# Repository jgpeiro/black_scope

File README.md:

# Black_scope
Low end oscilloscope based on STM32G4

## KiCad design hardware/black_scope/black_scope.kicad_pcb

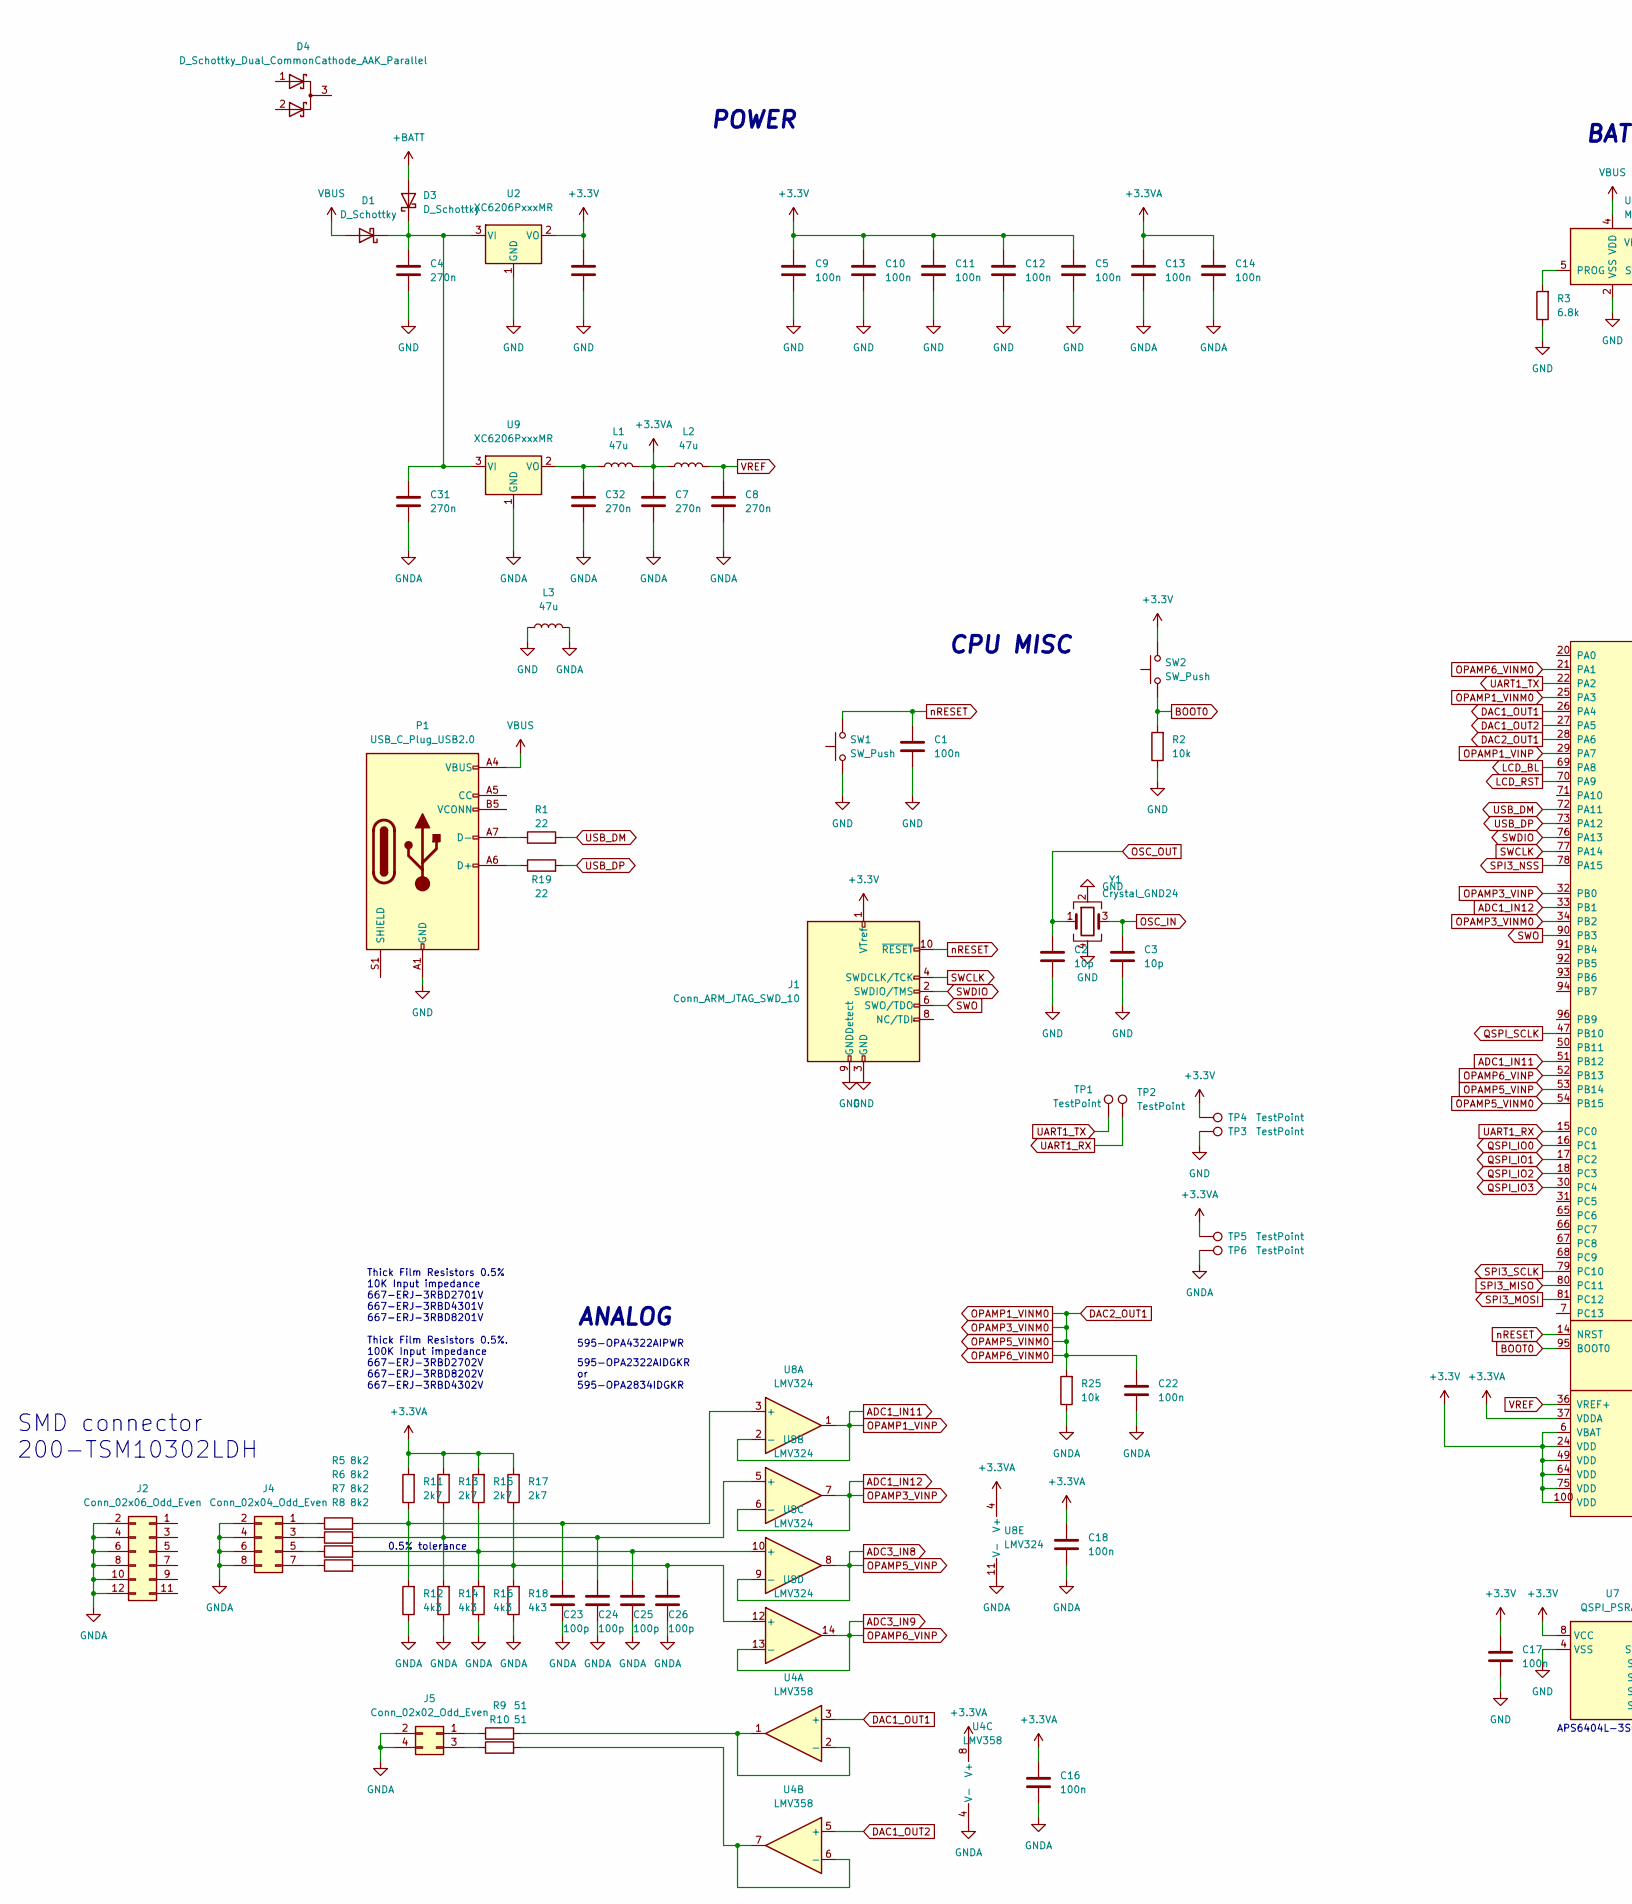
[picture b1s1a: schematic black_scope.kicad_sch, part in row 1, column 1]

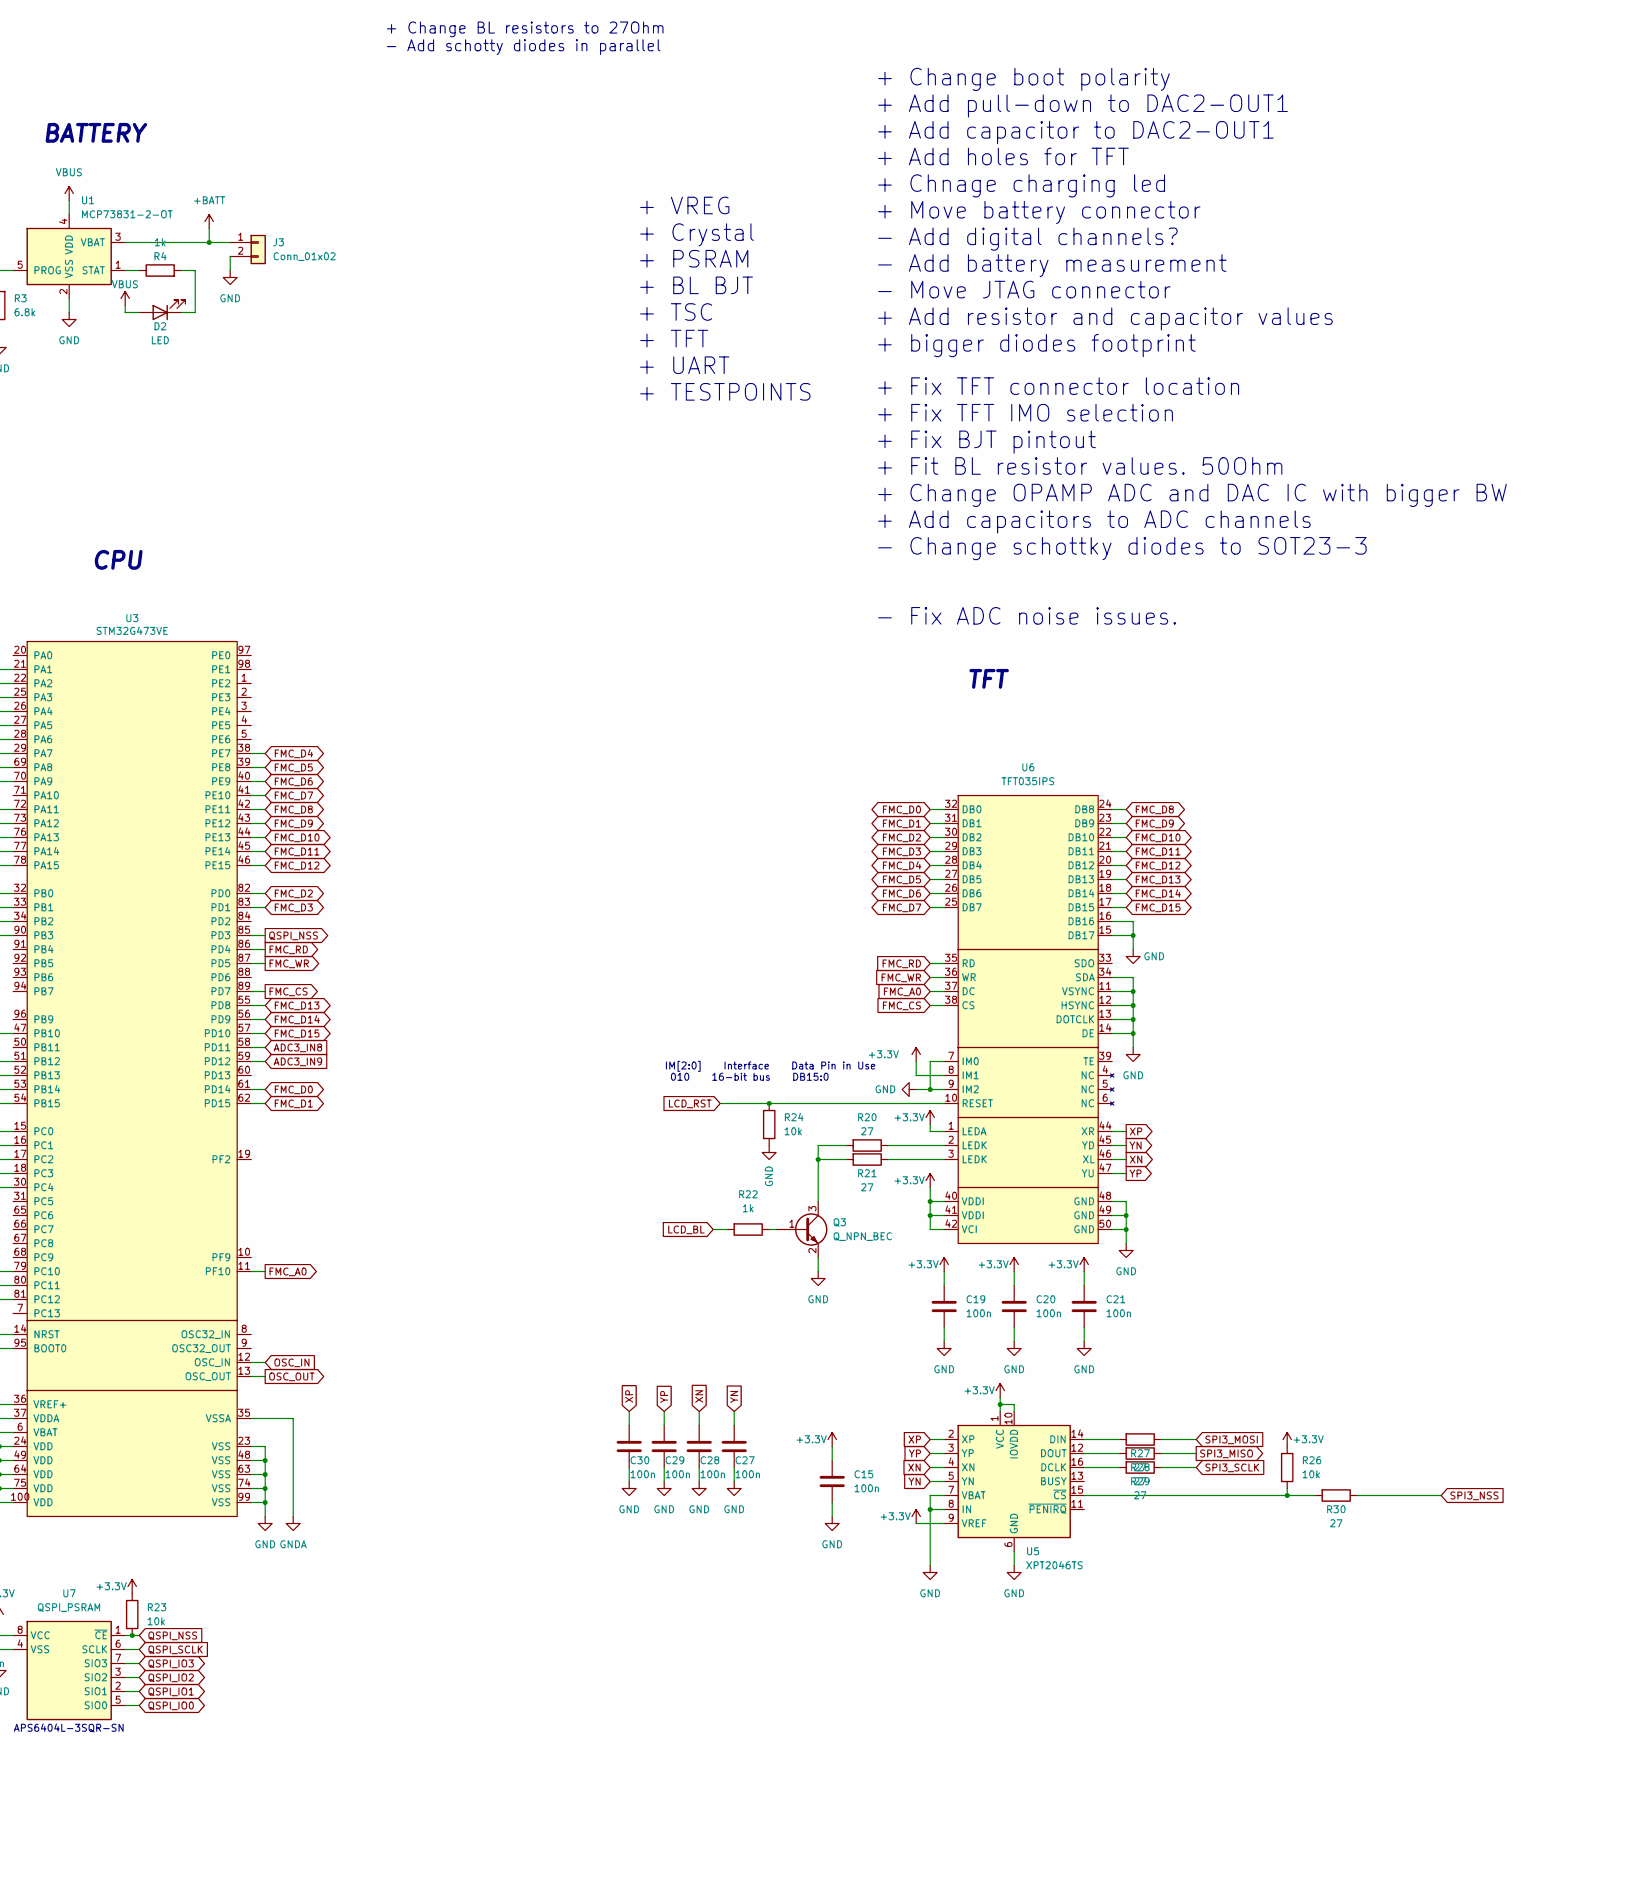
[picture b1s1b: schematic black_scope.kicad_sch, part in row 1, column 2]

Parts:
C1, C5, C9, C10, C11, C12, C13, C14, C15, C16, C17, C18, C19, C20, C21, C22, C27, C28, C29, C30: 100n; C_0603_1608Metric_Pad1.08x0.95mm_HandSolder
C2, C3: 10p; C_0603_1608Metric_Pad1.08x0.95mm_HandSolder
C4, C6, C7, C8, C31, C32: 270n; C_0603_1608Metric_Pad1.08x0.95mm_HandSolder
C23, C24, C25, C26: 100p; C_0603_1608Metric_Pad1.08x0.95mm_HandSolder
D1, D3: D_Schottky; D_1206_3216Metric_Pad1.42x1.75mm_HandSolder; Mouser REF 512-SS24FL
D2: LED; D_0603_1608Metric_Pad1.05x0.95mm_HandSolder
D4: D_Schottky_Dual_CommonCathode_AAK_Parallel; SOT-23; Mouser REF 750-BAT54C-HF
J1: Conn_ARM_JTAG_SWD_10; PinHeader_2x05_P1.27mm_Vertical_SMD; Mouser REF 649-221121-00010T4LF
J2: Conn_02x06_Odd_Even; PinHeader_2x06_P2.54mm_Vertical_SMD; Mouser REF 200-TSM10302LDH
J3: Conn_01x02; JST_PH_B2B-PH-K_1x02_P2.00mm_Vertical
J4: Conn_02x04_Odd_Even; PinHeader_2x04_P2.54mm_Horizontal
J5: Conn_02x02_Odd_Even; PinHeader_2x02_P2.54mm_Horizontal
L1, L2, L3: 47u; L_0603_1608Metric_Pad1.05x0.95mm_HandSolder; Mouser REF 80-L0603B470KPWFT
P1: USB_C_Plug_USB2.0; USB_C_Receptacle_HRO_TYPE-C-31-M-12; Mouser REF 640-USB4105-GF-A
Q3: Q_NPN_BEC; SOT-23; Mouser REF 750-SS8050-G
R1, R19: 22; R_0603_1608Metric_Pad0.98x0.95mm_HandSolder
R2, R23, R24, R25, R26: 10k; R_0603_1608Metric_Pad0.98x0.95mm_HandSolder
R3: 6.8k; R_0603_1608Metric_Pad0.98x0.95mm_HandSolder
R4, R22: 1k; R_0603_1608Metric_Pad0.98x0.95mm_HandSolder
R5, R6, R7, R8: 8k2; R_0603_1608Metric_Pad0.98x0.95mm_HandSolder; Mouser REF 667-ERJ-3RBD8201V
R9, R10: 51; R_0603_1608Metric_Pad0.98x0.95mm_HandSolder
R11, R13, R15, R17: 2k7; R_0603_1608Metric_Pad0.98x0.95mm_HandSolder; Mouser REF 667-ERJ-3RBD2701V
R12, R14, R16, R18: 4k3; R_0603_1608Metric_Pad0.98x0.95mm_HandSolder; Mouser REF 667-ERJ-3RBD4301V
R20, R21, R27, R28, R29, R30: 27; R_0603_1608Metric_Pad0.98x0.95mm_HandSolder
SW1, SW2: SW_Push; SW_Push_SPST_NO_Alps_SKRK; Mouser REF 688-SKRKAHE010
TP1, TP2, TP3, TP4, TP5, TP6: TestPoint; TestPoint_Pad_D1.0mm
U1: MCP73831-2-OT; SOT-23-5; Mouser REF 579-MCP73831T-2DCIOT
U2, U9: XC6206PxxxMR; SOT-23-3; Mouser REF 579-MCP1700T3302E/TT
U3: STM32G473VE; LQFP-100_14x14mm_P0.5mm; Mouser REF 511-STM32G473VET6
U4: LMV358; TSSOP-8_4.4x3mm_P0.65mm; Mouser REF 595-LMV358IDR
U5: XPT2046TS; TSSOP-16_4.4x5mm_P0.65mm; Mouser REF 595-TSC2046EIPWR
U6: TFT035IPS; Hirose_FH12-50S-0.5SH_1x50-1MP_P0.50mm_Horizontal; Mouser REF 649-62684-50210E9ALF
U7: QSPI_PSRAM; SOIC-8_3.9x4.9mm_P1.27mm; Mouser REF 878-APS6404L-3SQR-SN
U8: LMV324; TSSOP-14_4.4x5mm_P0.65mm; Mouser REF 595-OPA4322AIPWR
Y1: Crystal_GND24; Crystal_SMD_3225-4Pin_3.2x2.5mm; Mouser REF 732-322524F20GAC0

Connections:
+3.3V: C5.1, C6.1, C9.1, C10.1, C11.1, C12.1, C15.1, C17.1, C19.1, C20.1, C21.1, J1.1 (VTref), R23.1, R26.1, SW2.2, TP4.1, U2.2 (VO), U3.6 (VBAT), U3.24 (VDD), U3.49 (VDD), U3.64 (VDD), U3.75 (VDD), U3.100 (VDD), U5.1 (VCC), U5.9 (VREF), U5.10 (IOVDD), U6.1 (LEDA), U6.8 (IM1), U6.40 (VDDI), U6.41 (VDDI), U6.42 (VCI), U7.8 (VCC)
+3.3VA: C7.1, C13.1, C14.1, C16.1, C18.1, L1.2, L2.1, R11.2, R13.2, R15.2, R17.2, TP5.1, U3.37 (VDDA), U4.8 (V+), U8.4 (V+)
+BATT: D3.2 (A), J3.1, U1.3 (VBAT)
ADC1_IN11: U3.29 (PA7), U3.51 (PB12), U8.1, U8.2 (-)
ADC1_IN12: U3.32 (PB0), U3.33 (PB1), U8.6 (-), U8.7
ADC3_IN8: U3.53 (PB14), U3.58 (PD11), U8.8, U8.9 (-)
ADC3_IN9: U3.52 (PB13), U3.59 (PD12), U8.13 (-), U8.14
BOOT0: R2.2, SW2.1, U3.95 (BOOT0)
DAC1_OUT1: U3.26 (PA4), U4.3 (+)
DAC1_OUT2: U3.27 (PA5), U4.5 (+)
DAC2_OUT1: C22.1, R25.2, U3.21 (PA1), U3.25 (PA3), U3.28 (PA6), U3.34 (PB2), U3.54 (PB15)
FMC_A0: U3.11 (PF10), U6.37 (DC)
FMC_CS: U3.89 (PD7), U6.38 (CS)
FMC_D0: U3.61 (PD14), U6.32 (DB0)
FMC_D1: U3.62 (PD15), U6.31 (DB1)
FMC_D2: U3.82 (PD0), U6.30 (DB2)
FMC_D3: U3.83 (PD1), U6.29 (DB3)
FMC_D4: U3.38 (PE7), U6.28 (DB4)
FMC_D5: U3.39 (PE8), U6.27 (DB5)
FMC_D6: U3.40 (PE9), U6.26 (DB6)
FMC_D7: U3.41 (PE10), U6.25 (DB7)
FMC_D8: U3.42 (PE11), U6.24 (DB8)
FMC_D9: U3.43 (PE12), U6.23 (DB9)
FMC_D10: U3.44 (PE13), U6.22 (DB10)
FMC_D11: U3.45 (PE14), U6.21 (DB11)
FMC_D12: U3.46 (PE15), U6.20 (DB12)
FMC_D13: U3.55 (PD8), U6.19 (DB13)
FMC_D14: U3.56 (PD9), U6.18 (DB14)
FMC_D15: U3.57 (PD10), U6.17 (DB15)
FMC_RD: U3.86 (PD4), U6.35 (RD)
FMC_WR: U3.87 (PD5), U6.36 (WR)
GND: C1.2, C2.2, C3.2, C4.2, C5.2, C6.2, C9.2, C10.2, C11.2, C12.2, C15.2, C17.2, C19.2, C20.2, C21.2, C27.2, C28.2, C29.2, C30.2, J1.3 (GND), J1.5 (GND), J1.9 (GNDDetect), J3.2, L3.1, P1.A1 (GND), P1.A12 (GND), P1.B1 (GND), P1.B12 (GND), Q3.2 (E), R2.1, R3.1, R24.2, SW1.1, TP3.1, U1.2 (VSS), U2.1 (GND), U3.23 (VSS), U3.48 (VSS), U3.63 (VSS), U3.74 (VSS), U3.99 (VSS), U5.6 (GND), U5.7 (VBAT), U5.8 (IN), U6.7 (IM0), U6.9 (IM2), U6.11 (VSYNC), U6.12 (HSYNC), U6.13 (DOTCLK), U6.14 (DE), U6.15 (DB17), U6.16 (DB16), U6.34 (SDA), U6.48 (GND), U6.49 (GND), U6.50 (GND), U7.4 (VSS), Y1.2, Y1.4
GNDA: C7.2, C8.2, C13.2, C14.2, C16.2, C18.2, C22.2, C23.2, C24.2, C25.2, C26.2, C31.2, C32.2, J2.2, J2.4, J2.6, J2.8, J2.10, J2.12, J4.2, J4.4, J4.6, J4.8, J5.2, J5.4, L3.2, R12.1, R14.1, R16.1, R18.1, R25.1, TP6.1, U3.35 (VSSA), U4.4 (V-), U8.11 (V-), U9.1 (GND)
LCD_BL: R22.2, U3.69 (PA8)
LCD_RST: R24.1, U3.70 (PA9), U6.10 (RESET)
unnamed: C4.1, C31.1, D1.1 (K), D3.1 (K), U2.3 (VI), U9.3 (VI)
unnamed: D2.1 (K), R4.2
unnamed: J4.1, R5.1
unnamed: J4.3, R6.1
unnamed: J4.5, R7.1
unnamed: J4.7, R8.1
unnamed: J5.1, R9.1
unnamed: J5.3, R10.1
unnamed: P1.A6 (D+), R19.1
unnamed: P1.A7 (D-), R1.1
unnamed: Q3.1 (B), R22.1
unnamed: Q3.3 (C), R20.2, R21.2
unnamed: R20.1, U6.2 (LEDK)
unnamed: R21.1, U6.3 (LEDK)
unnamed: R3.2, U1.5 (PROG)
unnamed: R4.1, U1.1 (STAT)
unnamed: R9.2, U4.1, U4.2 (-)
unnamed: R10.2, U4.6 (-), U4.7
unnamed: R29.2, U5.16 (DCLK)
unnamed: R27.2, U5.14 (DIN)
unnamed: R28.2, U5.12 (DOUT)
unnamed: R26.2, R30.2, U5.15 (~CS)
unnamed: C23.1, R5.2, R11.1, R12.2, U8.3 (+)
unnamed: C24.1, R6.2, R13.1, R14.2, U8.5 (+)
unnamed: C25.1, R7.2, R15.1, R16.2, U8.10 (+)
unnamed: C26.1, R8.2, R17.1, R18.2, U8.12 (+)
unnamed: C32.1, L1.1, U9.2 (VO)
OSC_IN: C3.1, U3.12 (OSC_IN), Y1.3
OSC_OUT: C2.1, U3.13 (OSC_OUT), Y1.1
QSPI_IO0: U3.16 (PC1), U7.5 (SIO0)
QSPI_IO1: U3.17 (PC2), U7.2 (SIO1)
QSPI_IO2: U3.18 (PC3), U7.3 (SIO2)
QSPI_IO3: U3.30 (PC4), U7.7 (SIO3)
QSPI_NSS: R23.2, U3.85 (PD3), U7.1 (~CE)
QSPI_SCLK: U3.47 (PB10), U7.6 (SCLK)
SPI3_MISO: R28.1, U3.80 (PC11)
SPI3_MOSI: R27.1, U3.81 (PC12)
SPI3_NSS: R30.1, U3.78 (PA15)
SPI3_SCLK: R29.1, U3.79 (PC10)
SWCLK: J1.4 (SWDCLK/TCK), U3.77 (PA14)
SWDIO: J1.2 (SWDIO/TMS), U3.76 (PA13)
SWO: J1.6 (SWO/TDO), U3.90 (PB3)
UART1_RX: TP2.1, U3.15 (PC0)
UART1_TX: TP1.1, U3.22 (PA2)
USB_DM: R1.2, U3.72 (PA11)
USB_DP: R19.2, U3.73 (PA12)
VBUS: D1.2 (A), D2.2 (A), P1.A4 (VBUS), P1.A9 (VBUS), P1.B4 (VBUS), P1.B9 (VBUS), U1.4 (VDD)
VREF: C8.1, L2.2, U3.36 (VREF+)
XN: C28.1, U5.4 (XN), U6.46 (XL)
XP: C30.1, U5.2 (XP), U6.44 (XR)
YN: C27.1, U5.5 (YN), U6.45 (YD)
YP: C29.1, U5.3 (YP), U6.47 (YU)
nRESET: C1.1, J1.10 (~RESET), SW1.2, U3.14 (NRST)

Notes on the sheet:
+ Change boot polarity + Add pull-down to DAC2-OUT1 + Add capacitor to DAC2-OUT1 + Add holes for TFT + Chnage charging led + Move battery connector - Add digital channels? - Add battery measurement - Move JTAG connector + Add resistor and capacitor values + bigger diodes footprint
APS6404L-3SQR-SN
0.5% tolerance
595-OPA4322AIPWR
CPU
SMD connector 200-TSM10302LDH
+ Fix TFT connector location + Fix TFT IMO selection + Fix BJT pintout + Fit BL resistor values. 50Ohm + Change OPAMP ADC and DAC IC with bigger BW + Add capacitors to ADC channels - Change schottky diodes to SOT23-3
ANALOG
POWER
+ VREG + Crystal + PSRAM + BL BJT + TSC + TFT + UART + TESTPOINTS
+ Change BL resistors to 27Ohm - Add schotty diodes in parallel
Thick Film Resistors 0.5% 10K Input impedance 667-ERJ-3RBD2701V 667-ERJ-3RBD4301V 667-ERJ-3RBD8201V Thick Film Resistors 0.5%. 100K Input impedance 667-ERJ-3RBD2702V 667-ERJ-3RBD8202V 667-ERJ-3RBD4302V
CPU MISC
IM[2:0] Interface Data Pin in Use 010 16-bit bus DB15:0
BATTERY
- Fix ADC noise issues.
TFT
595-OPA2322AIDGKR or 595-OPA2834IDGKR

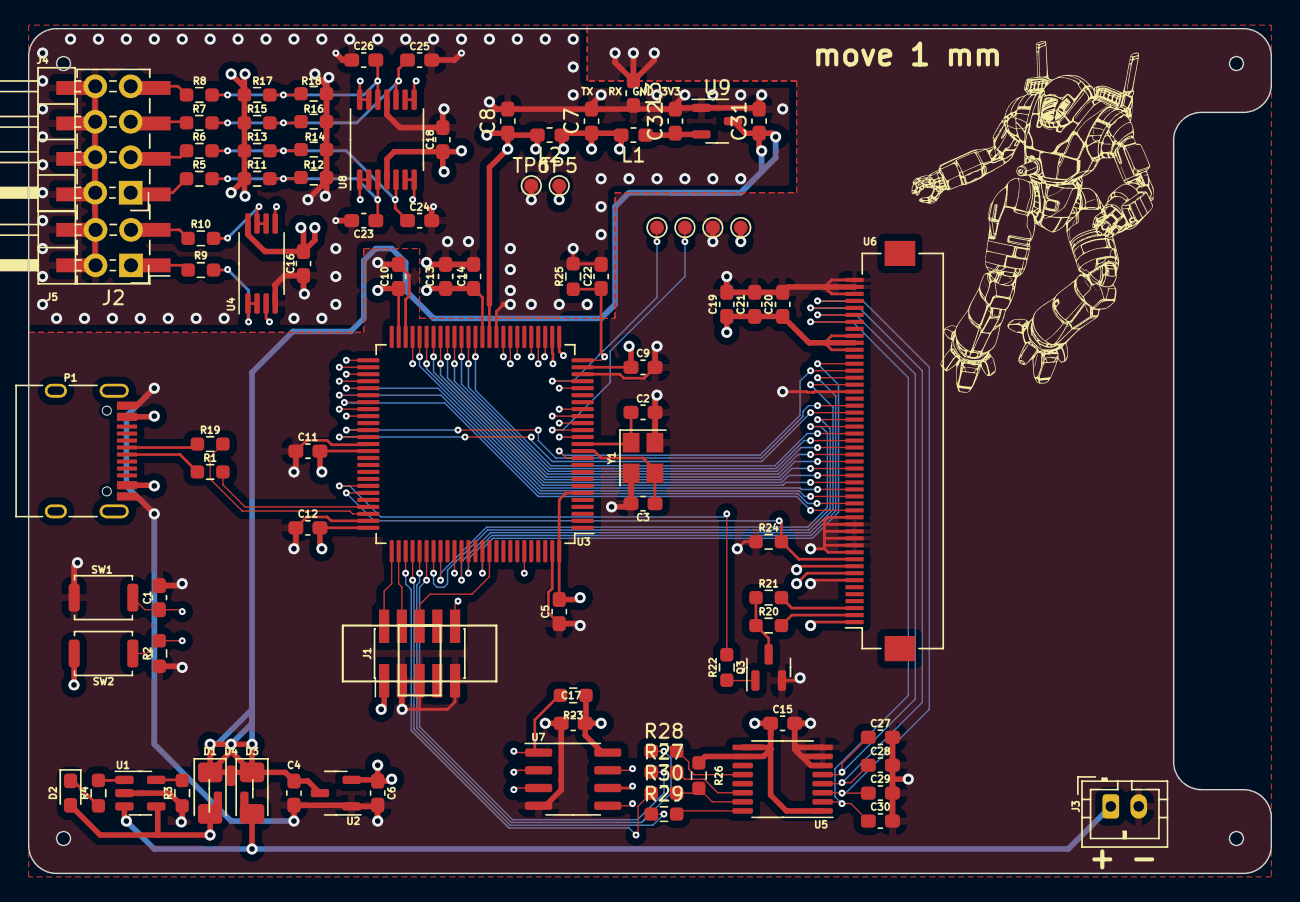
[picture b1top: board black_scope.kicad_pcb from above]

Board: 4 copper layers, 89.0 x 60.5 mm, 94 parts (0 on the bottom side), 88 nets.

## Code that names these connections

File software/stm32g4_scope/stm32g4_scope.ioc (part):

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Mcu.Name=STM32G473V(B-C-E)Tx
Mcu.Package=LQFP100
Mcu.UserName=STM32G473VETx
PA1.Mode=PGA Internally connected_IO0_BIAS
PA1.Signal=OPAMP6_VINM0
PA11.Mode=Device
PA11.Signal=USB_DM
PA12.Mode=Device
PA12.Signal=USB_DP
PA13.Mode=Trace_Asynchronous_SW
PA13.Signal=SYS_JTMS-SWDIO
PA14.Mode=Trace_Asynchronous_SW
PA14.Signal=SYS_JTCK-SWCLK
PA15.GPIOParameters=GPIO_Label
PA15.GPIO_Label=TSC_nSS
PA15.Signal=GPIO_Output
PA3.Mode=PGA Internally connected_IO0_BIAS
PA3.Signal=OPAMP1_VINM0
PA4.Signal=COMP_DAC11_group
PA5.Signal=COMP_DAC12_group
PA6.Signal=COMP_DAC21_group
PA7.Mode=PGA Internally connected_IO0_BIAS
PA7.Signal=OPAMP1_VINP
PA8.GPIOParameters=GPIO_Label
PA8.GPIO_Label=LCD_BL
PA8.Signal=GPIO_Output
PA9.GPIOParameters=GPIO_Label
PA9.GPIO_Label=LCD_nRST
PA9.Signal=GPIO_Output
PB0.Mode=PGA Internally connected_IO0_BIAS
PB0.Signal=OPAMP3_VINP
PB10.GPIOParameters=GPIO_Speed
PB10.GPIO_Speed=GPIO_SPEED_FREQ_VERY_HIGH
PB10.Mode=Single Bank 2
PB10.Signal=QUADSPI1_CLK
PB13.Mode=PGA Internally connected_IO0_BIAS
PB13.Signal=OPAMP6_VINP
PB14.Mode=PGA Internally connected_IO0_BIAS
PB14.Signal=OPAMP5_VINP
PB15.Mode=PGA Internally connected_IO0_BIAS
PB15.Signal=OPAMP5_VINM0
PB2.Mode=PGA Internally connected_IO0_BIAS
PB2.Signal=OPAMP3_VINM0
PB3.Mode=Trace_Asynchronous_SW
PB3.Signal=SYS_JTDO-SWO
PC1.GPIOParameters=GPIO_Speed
PC1.GPIO_Speed=GPIO_SPEED_FREQ_VERY_HIGH
PC1.Mode=Single Bank 2
PC1.Signal=QUADSPI1_BK2_IO0
PC10.Mode=Full_Duplex_Master
PC10.Signal=SPI3_SCK
PC11.Mode=Full_Duplex_Master
PC11.Signal=SPI3_MISO
PC12.Mode=Full_Duplex_Master
PC12.Signal=SPI3_MOSI
PC2.GPIOParameters=GPIO_Speed
PC2.GPIO_Speed=GPIO_SPEED_FREQ_VERY_HIGH
PC2.Mode=Single Bank 2
PC2.Signal=QUADSPI1_BK2_IO1
PC3.GPIOParameters=GPIO_Speed
PC3.GPIO_Speed=GPIO_SPEED_FREQ_VERY_HIGH
PC3.Mode=Single Bank 2
PC3.Signal=QUADSPI1_BK2_IO2
PC4.GPIOParameters=GPIO_Speed
PC4.GPIO_Speed=GPIO_SPEED_FREQ_VERY_HIGH
PC4.Mode=Single Bank 2
PC4.Signal=QUADSPI1_BK2_IO3
PD0.Mode=16b-d1
PD0.Signal=FMC_D2
PD1.Mode=16b-d1
PD1.Signal=FMC_D3
PD10.Mode=16b-d1
PD10.Signal=FMC_D15
PD14.Mode=16b-d1
PD14.Signal=FMC_D0
PD15.Mode=16b-d1
PD15.Signal=FMC_D1
PD3.GPIOParameters=GPIO_Speed
PD3.GPIO_Speed=GPIO_SPEED_FREQ_VERY_HIGH
PD3.Mode=Single Bank 2
PD3.Signal=QUADSPI1_BK2_NCS
PD4.Mode=Lcd1
PD4.Signal=FMC_NOE
PD5.Mode=Lcd1
PD5.Signal=FMC_NWE
PD7.Mode=NorPsramChipSelect1_1
PD7.Signal=FMC_NE1
PD8.Mode=16b-d1
PD8.Signal=FMC_D13
PD9.Mode=16b-d1
PD9.Signal=FMC_D14
PE10.Mode=16b-d1
PE10.Signal=FMC_D7
PE11.Mode=16b-d1
PE11.Signal=FMC_D8
PE12.Mode=16b-d1
PE12.Signal=FMC_D9
PE13.Mode=16b-d1
PE13.Signal=FMC_D10
PE14.Mode=16b-d1
PE14.Signal=FMC_D11
PE15.Mode=16b-d1
PE15.Signal=FMC_D12
PE7.Mode=16b-d1
PE7.Signal=FMC_D4
PE8.Mode=16b-d1
PE8.Signal=FMC_D5
PE9.Mode=16b-d1
PE9.Signal=FMC_D6
PF0-OSC_IN.Mode=HSE-External-Oscillator
PF0-OSC_IN.Signal=RCC_OSC_IN
PF1-OSC_OUT.Mode=HSE-External-Oscillator
PF1-OSC_OUT.Signal=RCC_OSC_OUT
PF10.Mode=A0_1
PF10.Signal=FMC_A0
RCC.HSE_VALUE=24000000
RCC.SYSCLKFreq_VALUE=170000000
RCC.SYSCLKSource=RCC_SYSCLKSOURCE_PLLCLK
board=custom

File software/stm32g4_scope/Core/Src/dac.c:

/* USER CODE BEGIN Header */
/**
  ******************************************************************************
  * @file    dac.c
  * @brief   This file provides code for the configuration
  *          of the DAC instances.
  ******************************************************************************
  * @attention
  *
  * Copyright (c) 2023 STMicroelectronics.
  * All rights reserved.
  *
  * This software is licensed under terms that can be found in the LICENSE file
  * in the root directory of this software component.
  * If no LICENSE file comes with this software, it is provided AS-IS.
  *
  ******************************************************************************
  */
/* USER CODE END Header */
/* Includes ------------------------------------------------------------------*/
#include "dac.h"

/* USER CODE BEGIN 0 */

/* USER CODE END 0 */

DAC_HandleTypeDef hdac1;
DAC_HandleTypeDef hdac2;
DMA_HandleTypeDef hdma_dac1_ch1;
DMA_HandleTypeDef hdma_dac1_ch2;

/* DAC1 init function */
void MX_DAC1_Init(void)
{

  /* USER CODE BEGIN DAC1_Init 0 */

  /* USER CODE END DAC1_Init 0 */

  DAC_ChannelConfTypeDef sConfig = {0};

  /* USER CODE BEGIN DAC1_Init 1 */

  /* USER CODE END DAC1_Init 1 */

  /** DAC Initialization
  */
  hdac1.Instance = DAC1;
  if (HAL_DAC_Init(&hdac1) != HAL_OK)
  {
    Error_Handler();
  }

  /** DAC channel OUT1 config
  */
  sConfig.DAC_HighFrequency = DAC_HIGH_FREQUENCY_INTERFACE_MODE_AUTOMATIC;
  sConfig.DAC_DMADoubleDataMode = DISABLE;
  sConfig.DAC_SignedFormat = DISABLE;
  sConfig.DAC_SampleAndHold = DAC_SAMPLEANDHOLD_DISABLE;
  sConfig.DAC_Trigger = DAC_TRIGGER_T4_TRGO;
  sConfig.DAC_Trigger2 = DAC_TRIGGER_NONE;
  sConfig.DAC_OutputBuffer = DAC_OUTPUTBUFFER_ENABLE;
  sConfig.DAC_ConnectOnChipPeripheral = DAC_CHIPCONNECT_EXTERNAL;
  sConfig.DAC_UserTrimming = DAC_TRIMMING_FACTORY;
  if (HAL_DAC_ConfigChannel(&hdac1, &sConfig, DAC_CHANNEL_1) != HAL_OK)
  {
    Error_Handler();
  }

  /** DAC channel OUT2 config
  */
  sConfig.DAC_Trigger = DAC_TRIGGER_T6_TRGO;
  if (HAL_DAC_ConfigChannel(&hdac1, &sConfig, DAC_CHANNEL_2) != HAL_OK)
  {
    Error_Handler();
  }
  /* USER CODE BEGIN DAC1_Init 2 */

  /* USER CODE END DAC1_Init 2 */

}
/* DAC2 init function */
void MX_DAC2_Init(void)
{

  /* USER CODE BEGIN DAC2_Init 0 */

  /* USER CODE END DAC2_Init 0 */

  DAC_ChannelConfTypeDef sConfig = {0};

  /* USER CODE BEGIN DAC2_Init 1 */

  /* USER CODE END DAC2_Init 1 */

  /** DAC Initialization
  */
  hdac2.Instance = DAC2;
  if (HAL_DAC_Init(&hdac2) != HAL_OK)
  {
    Error_Handler();
  }

  /** DAC channel OUT1 config
  */
  sConfig.DAC_HighFrequency = DAC_HIGH_FREQUENCY_INTERFACE_MODE_AUTOMATIC;
  sConfig.DAC_DMADoubleDataMode = DISABLE;
  sConfig.DAC_SignedFormat = DISABLE;
  sConfig.DAC_SampleAndHold = DAC_SAMPLEANDHOLD_DISABLE;
  sConfig.DAC_Trigger = DAC_TRIGGER_NONE;
  sConfig.DAC_Trigger2 = DAC_TRIGGER_NONE;
  sConfig.DAC_OutputBuffer = DAC_OUTPUTBUFFER_ENABLE;
  sConfig.DAC_ConnectOnChipPeripheral = DAC_CHIPCONNECT_EXTERNAL;
  sConfig.DAC_UserTrimming = DAC_TRIMMING_FACTORY;
  if (HAL_DAC_ConfigChannel(&hdac2, &sConfig, DAC_CHANNEL_1) != HAL_OK)
  {
    Error_Handler();
  }
  /* USER CODE BEGIN DAC2_Init 2 */

  /* USER CODE END DAC2_Init 2 */

}

void HAL_DAC_MspInit(DAC_HandleTypeDef* dacHandle)
{

  GPIO_InitTypeDef GPIO_InitStruct = {0};
  if(dacHandle->Instance==DAC1)
  {
  /* USER CODE BEGIN DAC1_MspInit 0 */

  /* USER CODE END DAC1_MspInit 0 */
    /* DAC1 clock enable */
    __HAL_RCC_DAC1_CLK_ENABLE();

    __HAL_RCC_GPIOA_CLK_ENABLE();
    /**DAC1 GPIO Configuration
    PA4     ------> DAC1_OUT1
    PA5     ------> DAC1_OUT2
    */
    GPIO_InitStruct.Pin = GPIO_PIN_4|GPIO_PIN_5;
    GPIO_InitStruct.Mode = GPIO_MODE_ANALOG;
    GPIO_InitStruct.Pull = GPIO_NOPULL;
    HAL_GPIO_Init(GPIOA, &GPIO_InitStruct);

    /* DAC1 DMA Init */
    /* DAC1_CH1 Init */
    hdma_dac1_ch1.Instance = DMA2_Channel1;
    hdma_dac1_ch1.Init.Request = DMA_REQUEST_DAC1_CHANNEL1;
    hdma_dac1_ch1.Init.Direction = DMA_MEMORY_TO_PERIPH;
    hdma_dac1_ch1.Init.PeriphInc = DMA_PINC_DISABLE;
    hdma_dac1_ch1.Init.MemInc = DMA_MINC_ENABLE;
    hdma_dac1_ch1.Init.PeriphDataAlignment = DMA_PDATAALIGN_WORD;
    hdma_dac1_ch1.Init.MemDataAlignment = DMA_MDATAALIGN_HALFWORD;
    hdma_dac1_ch1.Init.Mode = DMA_CIRCULAR;
    hdma_dac1_ch1.Init.Priority = DMA_PRIORITY_LOW;
    if (HAL_DMA_Init(&hdma_dac1_ch1) != HAL_OK)
    {
      Error_Handler();
    }

    __HAL_LINKDMA(dacHandle,DMA_Handle1,hdma_dac1_ch1);

    /* DAC1_CH2 Init */
    hdma_dac1_ch2.Instance = DMA2_Channel2;
    hdma_dac1_ch2.Init.Request = DMA_REQUEST_DAC1_CHANNEL2;
    hdma_dac1_ch2.Init.Direction = DMA_MEMORY_TO_PERIPH;
    hdma_dac1_ch2.Init.PeriphInc = DMA_PINC_DISABLE;
    hdma_dac1_ch2.Init.MemInc = DMA_MINC_ENABLE;
    hdma_dac1_ch2.Init.PeriphDataAlignment = DMA_PDATAALIGN_WORD;
    hdma_dac1_ch2.Init.MemDataAlignment = DMA_MDATAALIGN_HALFWORD;
    hdma_dac1_ch2.Init.Mode = DMA_CIRCULAR;
    hdma_dac1_ch2.Init.Priority = DMA_PRIORITY_LOW;
    if (HAL_DMA_Init(&hdma_dac1_ch2) != HAL_OK)
    {
      Error_Handler();
    }

    __HAL_LINKDMA(dacHandle,DMA_Handle2,hdma_dac1_ch2);

  /* USER CODE BEGIN DAC1_MspInit 1 */

  /* USER CODE END DAC1_MspInit 1 */
  }
  else if(dacHandle->Instance==DAC2)
  {
  /* USER CODE BEGIN DAC2_MspInit 0 */

  /* USER CODE END DAC2_MspInit 0 */
    /* DAC2 clock enable */
    __HAL_RCC_DAC2_CLK_ENABLE();

    __HAL_RCC_GPIOA_CLK_ENABLE();
    /**DAC2 GPIO Configuration
    PA6     ------> DAC2_OUT1
    */
    GPIO_InitStruct.Pin = GPIO_PIN_6;
    GPIO_InitStruct.Mode = GPIO_MODE_ANALOG;
    GPIO_InitStruct.Pull = GPIO_NOPULL;
    HAL_GPIO_Init(GPIOA, &GPIO_InitStruct);

  /* USER CODE BEGIN DAC2_MspInit 1 */

  /* USER CODE END DAC2_MspInit 1 */
  }
}

void HAL_DAC_MspDeInit(DAC_HandleTypeDef* dacHandle)
{

  if(dacHandle->Instance==DAC1)
  {
  /* USER CODE BEGIN DAC1_MspDeInit 0 */

  /* USER CODE END DAC1_MspDeInit 0 */
    /* Peripheral clock disable */
    __HAL_RCC_DAC1_CLK_DISABLE();

    /**DAC1 GPIO Configuration
    PA4     ------> DAC1_OUT1
    PA5     ------> DAC1_OUT2
    */
    HAL_GPIO_DeInit(GPIOA, GPIO_PIN_4|GPIO_PIN_5);

    /* DAC1 DMA DeInit */
    HAL_DMA_DeInit(dacHandle->DMA_Handle1);
    HAL_DMA_DeInit(dacHandle->DMA_Handle2);
  /* USER CODE BEGIN DAC1_MspDeInit 1 */

  /* USER CODE END DAC1_MspDeInit 1 */
  }
  else if(dacHandle->Instance==DAC2)
  {
  /* USER CODE BEGIN DAC2_MspDeInit 0 */

  /* USER CODE END DAC2_MspDeInit 0 */
    /* Peripheral clock disable */
    __HAL_RCC_DAC2_CLK_DISABLE();

    /**DAC2 GPIO Configuration
    PA6     ------> DAC2_OUT1
    */
    HAL_GPIO_DeInit(GPIOA, GPIO_PIN_6);

  /* USER CODE BEGIN DAC2_MspDeInit 1 */

  /* USER CODE END DAC2_MspDeInit 1 */
  }
}

/* USER CODE BEGIN 1 */

/* USER CODE END 1 */

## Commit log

2023-06-03 - Initial commit
2023-06-04 - Added scope_gui.jpg image
2023-06-29 - Added images
2023-07-11 - Added software folder
2023-07-16 - Update fw
2023-07-16 - Rename images
2023-07-17 - Update touch screen reading routines
2023-07-17 - Update UI
2023-07-18 - Update framebuffer
2023-07-20 - Fix PCB issues - Add datasheets
2023-07-20 - Gerber files v2
2023-07-21 - Improve FPS
2023-07-22 - Update DMAs
2023-07-23 - Added refence manual - Change optimization to -O1 - Set LCD pointers as volatile - Set scope members as volatile
2023-07-23 - Added lcd class
2023-07-23 - Remove debug folder - Add lcd.c
2023-07-23 - Refactor fonts and framebuf
2023-07-23 - Remove font 8x8
2023-07-25 - Move char draw functions to the font - Add FB on the scope to draw on screen text
2023-07-25 - Added tools.h/.c - Enable FIFO in FSMC write operations - Change optimization level to -Ofast
2023-07-27 - Added v2 version, with 16bit LCD and FreeRTOS
2023-07-28 - Added PSRAM with QSPI - Added nuklear theme - Added 3d case generated with YAPP_Box
2023-07-28 - Remove debug dir
2023-07-29 - Change QUAD_SPI pins to hig speed - Added opamp calibration - Handle opamps from UI - Handle offset from UI - Clamp x and y to max and min in LCD set pixel - Add function to draw adc data
2023-07-30 - Add draw_grid function - Use set window in the LCD - Move TSC as a separate task - Add low pass filter to the TSC and a touch count threshold
2023-07-30 - Added tools.c .h - Added on-screen measurements
2023-07-31 - Added wavegen - Change buf param to uint16_t in the lcd and fb
2023-08-01 - Added ui to handle the GUI - Update FMC timmings to "0" and reach 40 FPS
2023-08-13 - Reduce buffers len to 512 and also timers one pulse values. - Move nuklear context as a global scope so it dont need to be in the freertos heap - FreeRTOS config, change configTOTAL_HEAP_SIZE from 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
2023-08-15 - Added config file. Still removed from compiling. - Update freertos heap. Retain the same value. - Add tim6 so DAC CH1 and CH2 can work at different freqs. - In app_freertos Reduce tasks heap size R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
    - Set dac ch2 to use tim6
    - enable tim6
    - fonts: set array as const
    - Add scope functions to init hw
    - update wavegen to handle two timers
2023-08-15 - Temporally increase freertos stack to 32k (during code generation) - Enable irqs for ADC 3, 4, 5 - Enable AWD in ADC 3, 4, 5 - Update task heap size (during code generation) - add ui and scope init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
2023-08-17 - Update draw_buffers function to avoid erase previously drawn data. - Remove radius when drawing rectangles with nuklear - Initialize timer in OC mode. - Stop opamps before calibration - substract h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
2023-08-20 - Recover freertos reduced stack and heap sizes - Trigger supported on channels 1 and 2. But not on ch 3 and 4.
2023-08-22 - .cproject: Change optimizaion to -Ofast - app_freertos.c Add defines for ADC and DAC BUFFER_LEN Add new x0 parameter to nk_draw_fb Add new line_height variable Move UI to the right side of the scre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
2023-08-23 - Came back to -O1 optimization - Added DMA1_ChannelX_CNDTR to get the trigger event - Remove CLAMP from lcd_set_window - Fix trigger for channels 3 and 4. It was the AWD OPAMP channels. - Added inte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
2023-08-26 - Improve architecture. Add new queues and tasks.
2023-08-26 - Added new wavegen version with its updated ui function
2023-08-26 - Complete the new wavegen module functionality
2023-08-26 - Added new _scope class with irqs. still not functional.
2023-08-26 - Move wavegen to its own module.
2023-08-27 - first working version of the scope v2. only one channel. still some issues with horizontal freq.
2023-08-27 - Improve TSC. Now it works perfect.
2023-08-28 - Move the new _tScope class to the scope.c/.h files and disable the old one.
2023-08-28 - Remove old ui functions
2023-08-29 - app_freertos.c: Added new wait_timeout_ms parameter - scope and it. Add new dma_cndtr parameter to the scope structure - lcd.h: Add color defines.
2023-08-29 - Update the drawing routines in the scope - Block the UI while there is no tsc events.
2023-08-30 - Remove old functionality from app_freertos - Improve drawing functions for scope and wavegen - Show avg fps in the ui
2023-08-31 - Added is_collapsed method. - Moved ui_init to ui file - Added colors to wavegen and scope
2023-08-31 - Split arr_freertos in multiple tasks - Pending re-generate the code
2023-08-31 - Added initial usb support - Improve drawin routines in the scope
2023-08-31 - added wavegen "streamming" to usb support
2023-08-31 - Fix scope_confi_horizontal and vertical issues. - Fail trial for correct signal horizontal offset drawing
2023-09-01 - Improve scope drawing system.
2023-09-01 - Fix issue during renderig
2023-09-02 - Add two new events when a menu or windows is collapsed. These events are handled in the ui and sent to the drivers. - The scope has initial support and is pending add to the wavegen.
2023-09-02 - Update code
2023-09-03 - Add draw_marker function. - Handle collapsed in scope
2023-09-03 - Software cleanup
2023-09-03 - Add is_visible and is_collapsed events to the wavegen
2023-09-04 - Move the tsc code from the task to the driver.
2023-09-04 - Move shared RTOS resources to scope_tasks.h
2023-09-04 - Added new ui_build_xxx and xxx_draw functions
2023-09-04 - Added trigged attrib to the scope - Fix draw_marker function. Still not finihed.
2023-09-05 - Add comments in a ST HAL style
2023-09-06 - Added plantuml simplified diagrams
2023-09-07 - Add tentative for freertos time stats - Added documentation to scope.c - Added documentation to scope.h - Added documentation to scope_draw.c - Added documentation to scope_draw.h - Reduce scope_wa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
2023-09-16 - Update code with multiple working in progress tasks
2024-01-02 Long time update
2024-01-02 - Added f401re version - Added lvgl version
2024-01-02 - Added diagrams
2024-01-09 - Remove wrong f401re folder - Add proper f401re folder with scope sw
2024-01-09 - Delete old blink project
